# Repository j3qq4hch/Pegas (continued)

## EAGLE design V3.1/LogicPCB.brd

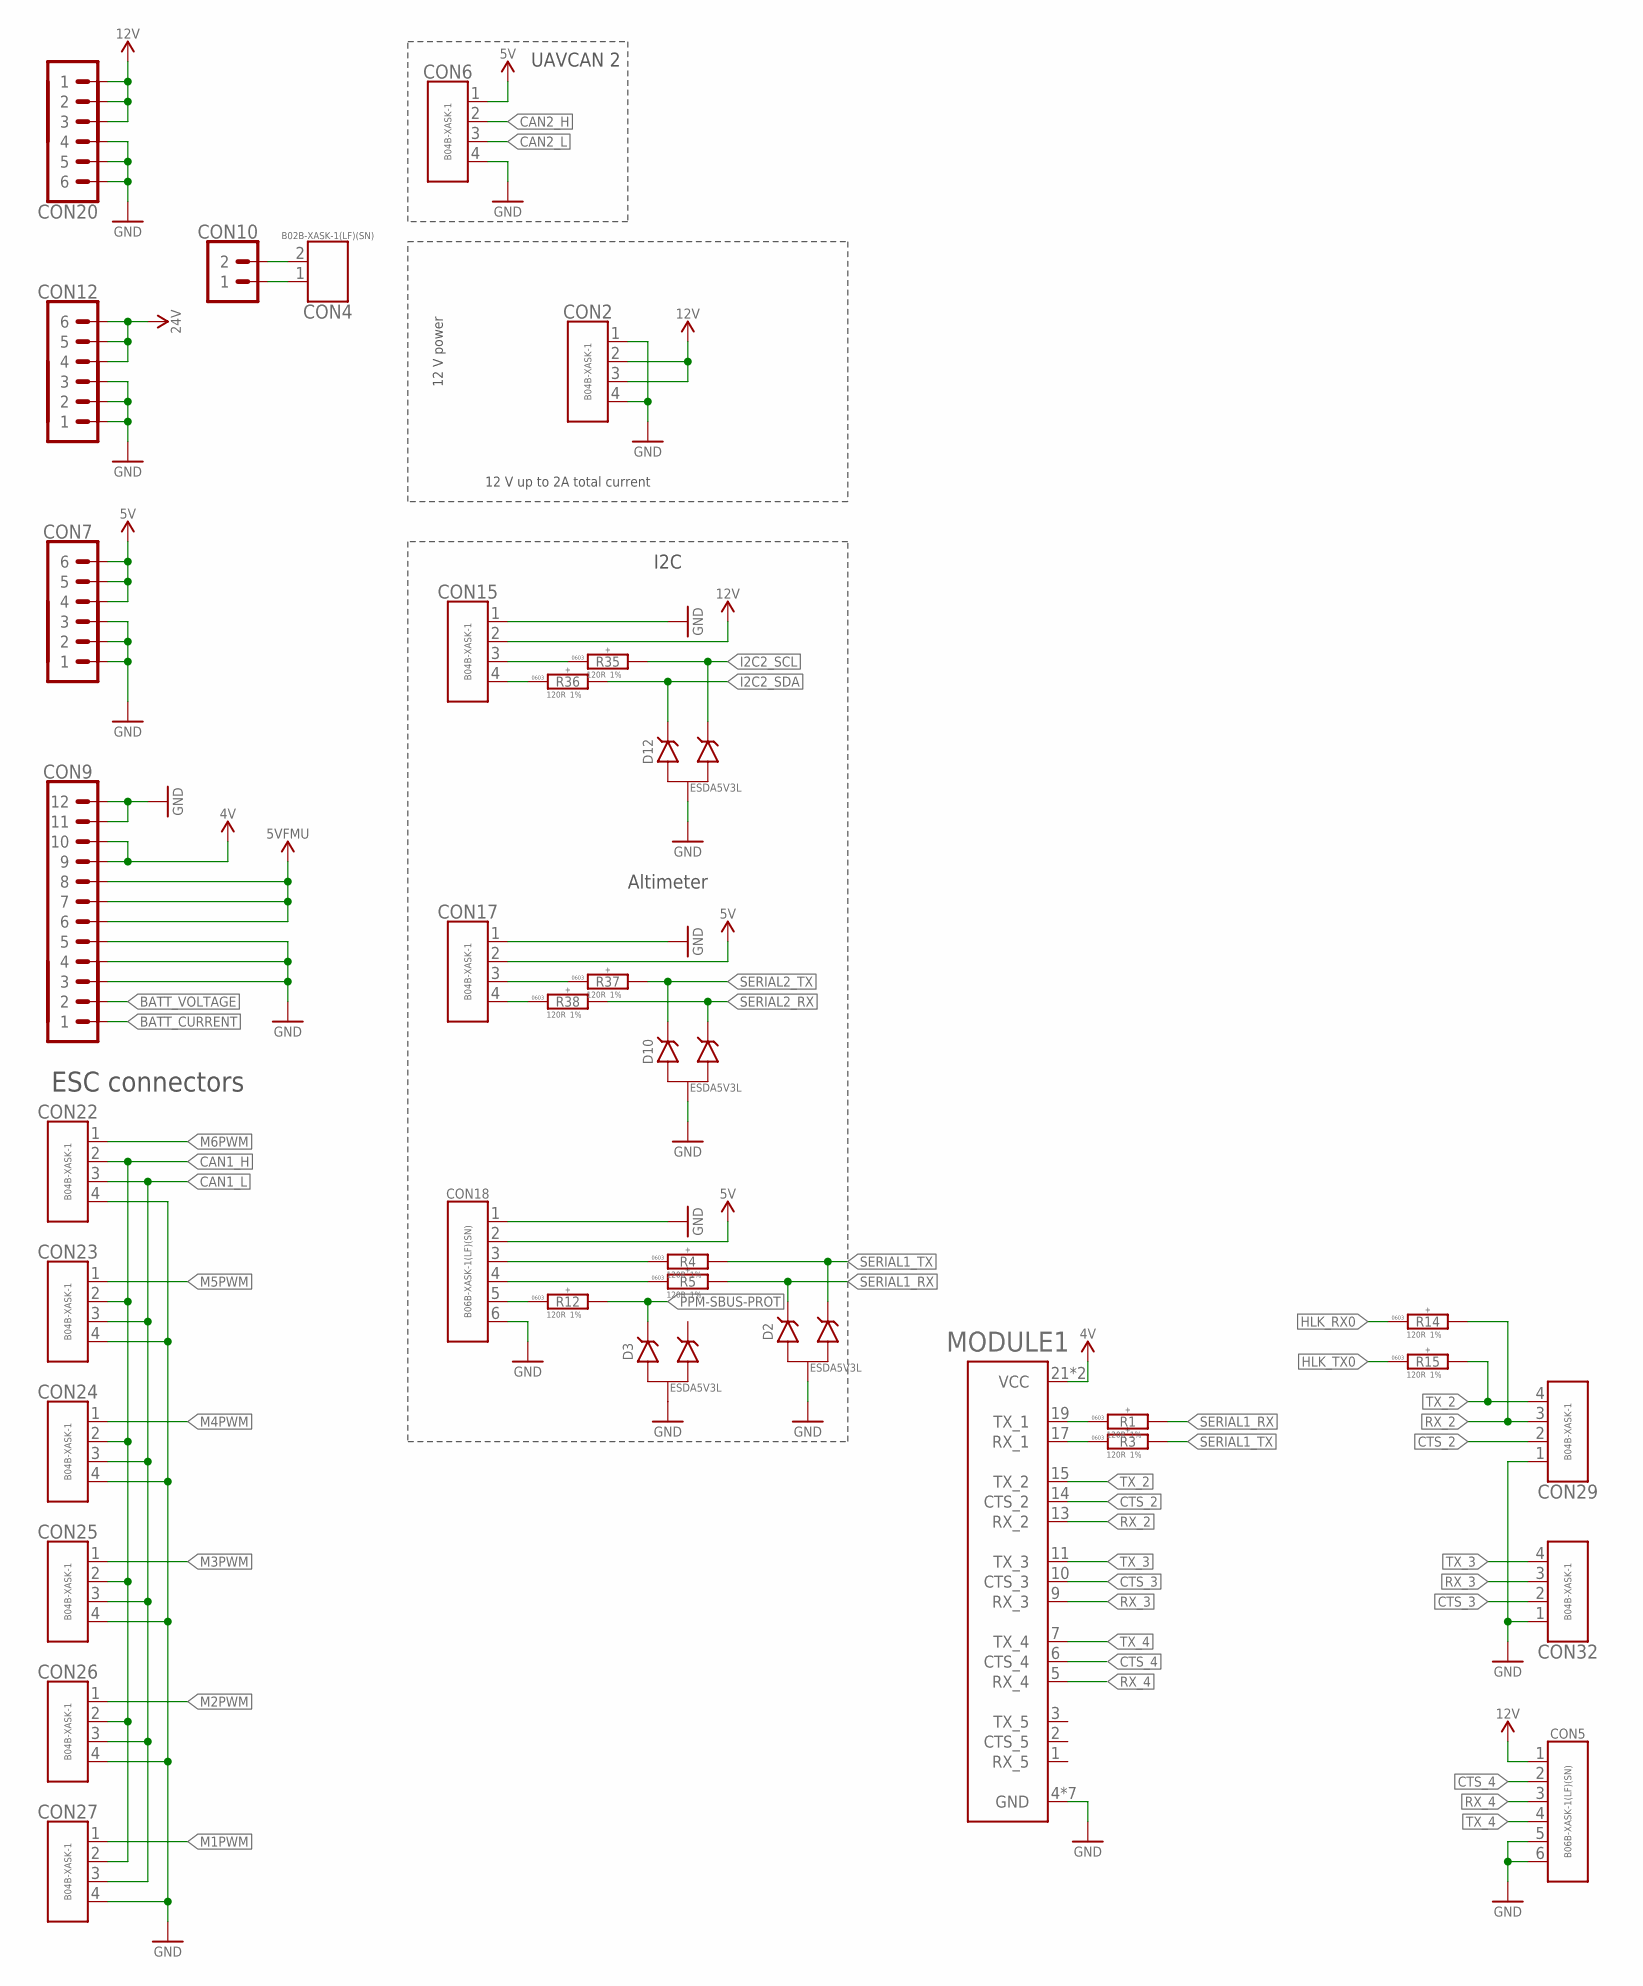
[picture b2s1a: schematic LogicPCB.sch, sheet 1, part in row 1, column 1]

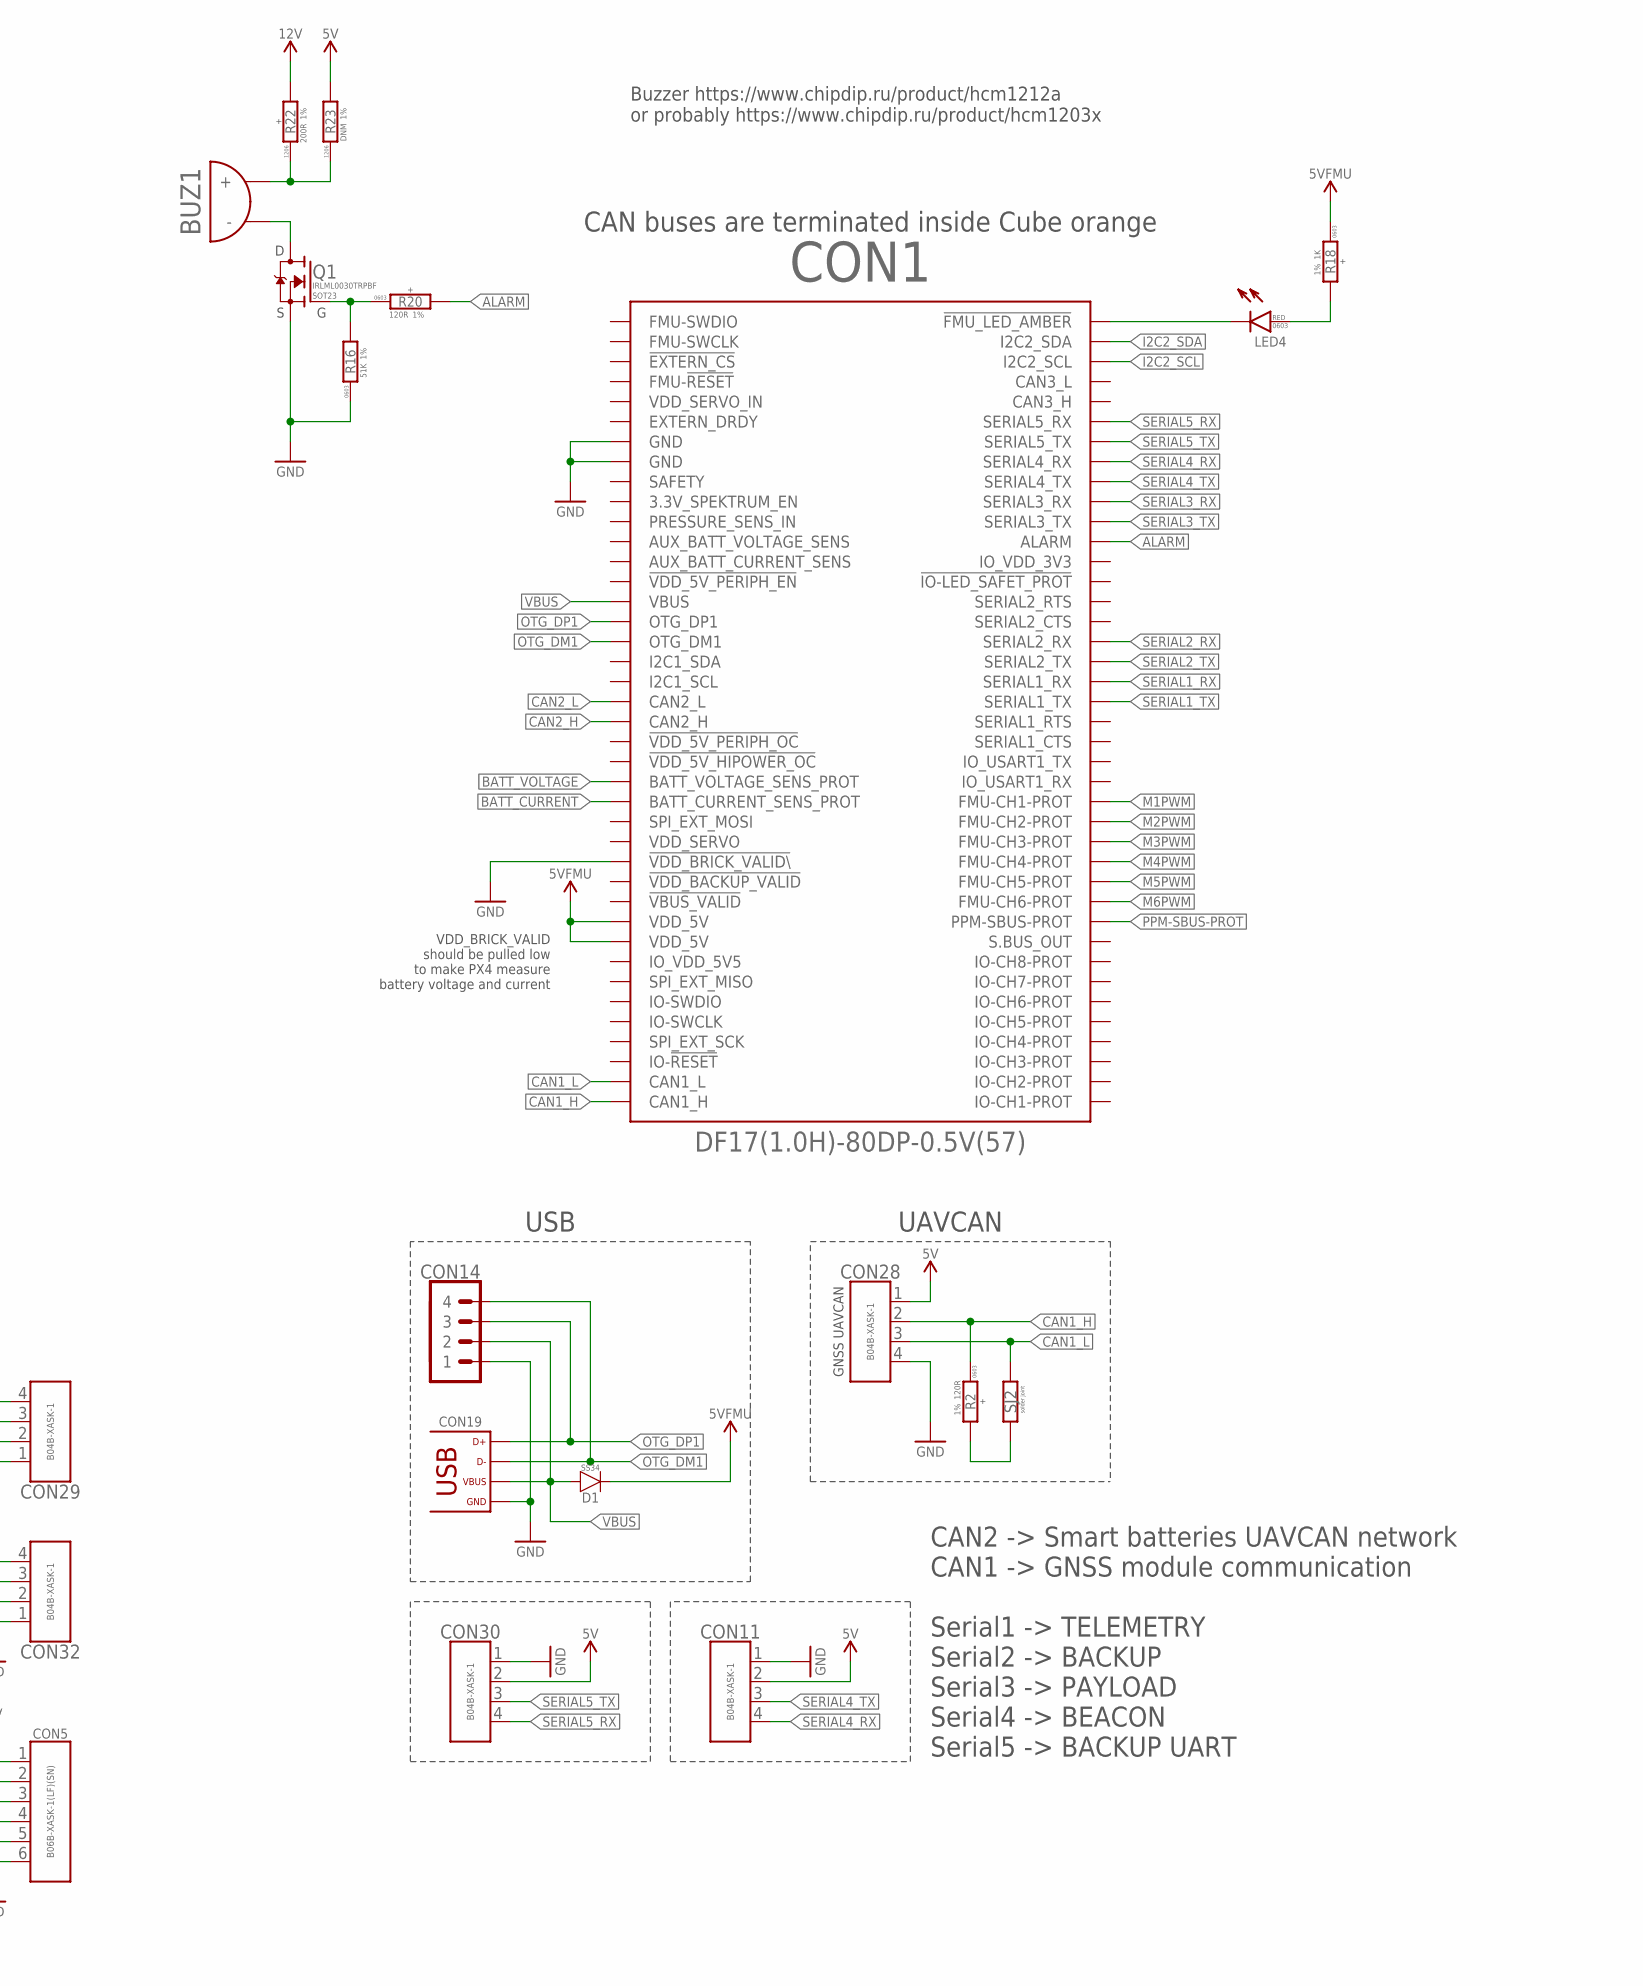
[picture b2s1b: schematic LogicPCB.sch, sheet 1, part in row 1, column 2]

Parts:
BUZ1: BUZZER-ЕР-12MM; BUZZER_12MM
CON1: CUBE_ORANGE_; CUBE_ORANGE
CON2, CON6, CON11, CON15, CON17, CON22, CON23, CON24, CON25, CON26, CON27, CON28, CON29, CON30, CON32: CON-4P-JST-XA; B04B-XASK-1
CON4: CON-2P-JST-XA; B02B-XASK-1
CON5, CON18: CON-6P-JST-XA; B06B-XASK-1
CON7, CON12, CON20: PINHEAD_1X06-2.54; 1X06-PTH-2.54
CON9: PINHEAD_1X12-2.54; 1X12-PTH-2.54
CON10: PINHEAD_1X02-2.54; 1X02-PTH-2.54
CON14: PINHEAD_1X04-2.54; 1X04-PTH-2.54
CON19: USB-TYPE-C-VERT-PROD; 2047110001-PROD; LCSC# C381139
D1: SS34; DO-214AC(SMA)
D2, D3, D10, D12: ESDA5V3L; SOT23B-3
LED4: LED-0603; LED0603; LCSC# C2286
MODULE1: MODEM_CARRIER
Q1: IRLML0030; SOT23
R1, R2, R3, R4, R5, R12, R14, R15, R20, R35, R36, R37, R38: 120R; R0603; LCSC# C22787
R16: 51K; R0603; LCSC# C23196
R18: 1K; R0603; LCSC# C21190
R22: 200R; R1206; LCSC# C25361
R23: DNM; R1206
SJ2: SOLDER_JOINT-SJ1; RES_0

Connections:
5VFMU: CON1.61 (VDD_5V), CON1.63 (VDD_5V), CON9.6, CON9.7, CON9.8, D1.C, R18.1
!FMU_LED_AMBER: CON1.2 (!FMU_LED_AMBER), LED4.C
ALARM: CON1.24 (ALARM), R20.2
BATT_CURRENT: CON1.49 (BATT_CURRENT_SENS_PROT), CON9.1
BATT_VOLTAGE: CON1.47 (BATT_VOLTAGE_SENS_PROT), CON9.2
CAN1_H: CON1.79 (CAN1_H), CON22.2, CON23.2, CON24.2, CON25.2, CON26.2, CON27.2, CON28.2, R2.1
CAN1_L: CON1.77 (CAN1_L), CON22.3, CON23.3, CON24.3, CON25.3, CON26.3, CON27.3, CON28.3, SJ2.2
CAN2_H: CON1.41 (CAN2_H), CON6.2
CAN2_L: CON1.39 (CAN2_L), CON6.3
CTS_2: CON29.2, MODULE1.14 (CTS_2)
CTS_3: CON32.2, MODULE1.10 (CTS_3)
CTS_4: CON5.2, MODULE1.6 (CTS_4)
GND: CON1.13 (GND), CON1.15 (GND), CON1.55 (!VDD_BRICK_VALID\), CON2.1, CON2.4, CON5.5, CON5.6, CON6.4, CON7.1, CON7.2, CON7.3, CON9.3, CON9.4, CON9.5, CON9.11, CON9.12, CON11.1, CON12.1, CON12.2, CON12.3, CON14.1, CON15.1, CON17.1, CON18.1, CON18.6, CON19.A1 (GND), CON19.A12 (GND), CON19.B1 (GND), CON19.B12 (GND), CON19.G1 (GND), CON19.G2 (GND), CON19.G4 (GND), CON19.G5 (GND), CON19.G7 (GND), CON19.G8 (GND), CON19.G9 (GND), CON19.G10 (GND), CON19.P$1 (GND), CON19.P$2 (GND), CON20.4, CON20.5, CON20.6, CON22.4, CON23.4, CON24.4, CON25.4, CON26.4, CON27.4, CON28.4, CON29.1, CON30.1, CON32.1, D2.3 (A), D3.3 (A), D10.3 (A), D12.3 (A), MODULE1.4 (GND), MODULE1.8 (GND), MODULE1.12 (GND), MODULE1.16 (GND), MODULE1.20 (GND), MODULE1.22 (GND), MODULE1.24 (GND), Q1.2 (S), R16.1; also elsewhere on the board
HLK_RX0: R14.1; also elsewhere on the board
HLK_TX0: R15.1; also elsewhere on the board
I2C2_SCL: CON1.6 (I2C2_SCL), D12.2 (C1), R35.2
I2C2_SDA: CON1.4 (I2C2_SDA), D12.1 (C), R36.2
M1PWM: CON1.50 (FMU-CH1-PROT), CON27.1
M2PWM: CON1.52 (FMU-CH2-PROT), CON26.1
M3PWM: CON1.54 (FMU-CH3-PROT), CON25.1
M4PWM: CON1.56 (FMU-CH4-PROT), CON24.1
M5PWM: CON1.58 (FMU-CH5-PROT), CON23.1
M6PWM: CON1.60 (FMU-CH6-PROT), CON22.1
unnamed: LED4.A, R18.2
unnamed: CON4.1, CON10.1
unnamed: BUZ1.2 (-), Q1.3 (D)
unnamed: MODULE1.19 (TX_1), R1.1
unnamed: Q1.1 (G), R16.2, R20.1
unnamed: MODULE1.17 (RX_1), R3.1
unnamed: CON4.2, CON10.2
unnamed: R2.2, SJ2.1
unnamed: CON18.3, R4.1
unnamed: CON18.4, R5.1
unnamed: BUZ1.1 (+), R22.P$1 (1), R23.P$1 (1)
unnamed: CON18.5, R12.1
unnamed: CON15.3, R35.1
unnamed: CON15.4, R36.1
unnamed: CON17.3, R37.1
unnamed: CON17.4, R38.1
OTG_DM1: CON1.33 (OTG_DM1), CON14.4, CON19.A7 (D-), CON19.B7 (D-)
OTG_DP1: CON1.31 (OTG_DP1), CON14.3, CON19.A6 (D+), CON19.B6 (D+)
PPM-SBUS-PROT: CON1.62 (PPM-SBUS-PROT), D3.1 (C), R12.2
RX_2: CON29.3, MODULE1.13 (RX_2), R14.2
RX_3: CON32.3, MODULE1.9 (RX_3)
RX_4: CON5.3, MODULE1.5 (RX_4)
SERIAL1_RX: CON1.38 (SERIAL1_RX), D2.1 (C), R1.2, R5.2; also elsewhere on the board
SERIAL1_TX: CON1.40 (SERIAL1_TX), D2.2 (C1), R3.2, R4.2; also elsewhere on the board
SERIAL2_RX: CON1.34 (SERIAL2_RX), D10.2 (C1), R38.2
SERIAL2_TX: CON1.36 (SERIAL2_TX), D10.1 (C), R37.2
SERIAL3_RX: CON1.20 (SERIAL3_RX); also elsewhere on the board
SERIAL3_TX: CON1.22 (SERIAL3_TX); also elsewhere on the board
SERIAL4_RX: CON1.16 (SERIAL4_RX), CON11.4
SERIAL4_TX: CON1.18 (SERIAL4_TX), CON11.3
SERIAL5_RX: CON1.12 (SERIAL5_RX), CON30.4
SERIAL5_TX: CON1.14 (SERIAL5_TX), CON30.3
TX_2: CON29.4, MODULE1.15 (TX_2), R15.2
TX_3: CON32.4, MODULE1.11 (TX_3)
TX_4: CON5.4, MODULE1.7 (TX_4)
VBUS: CON1.29 (VBUS), CON14.2, CON19.A4 (VBUS), CON19.B4 (VBUS), D1.A
VDD_4V: CON9.9, CON9.10, MODULE1.21 (VCC), MODULE1.23 (VCC)
VDD_5V: CON6.1, CON7.4, CON7.5, CON7.6, CON11.2, CON17.2, CON18.2, CON28.1, CON30.2, R23.P$2 (2)
VDD_12V: CON2.2, CON2.3, CON5.1, CON15.2, CON20.1, CON20.2, CON20.3, R22.P$2 (2); also elsewhere on the board
VDD_24V: CON12.4, CON12.5, CON12.6; also elsewhere on the board

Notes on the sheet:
12 V up to 2A total current
12 V power
GNSS UAVCAN
UAVCAN
UAVCAN 2
CAN buses are terminated inside Cube orange
CAN2 -> Smart batteries UAVCAN network CAN1 -> GNSS module communication Serial1 -> TELEMETRY Serial2 -> BACKUP Serial3 -> PAYLOAD Serial4 -> BEACON Serial5 -> BACKUP UART
USB
VDD_BRICK_VALID should be pulled low to make PX4 measure battery voltage and current
Buzzer https://www.chipdip.ru/product/hcm1212a or probably https://www.chipdip.ru/product/hcm1203x
ESC connectors
Altimeter
I2C

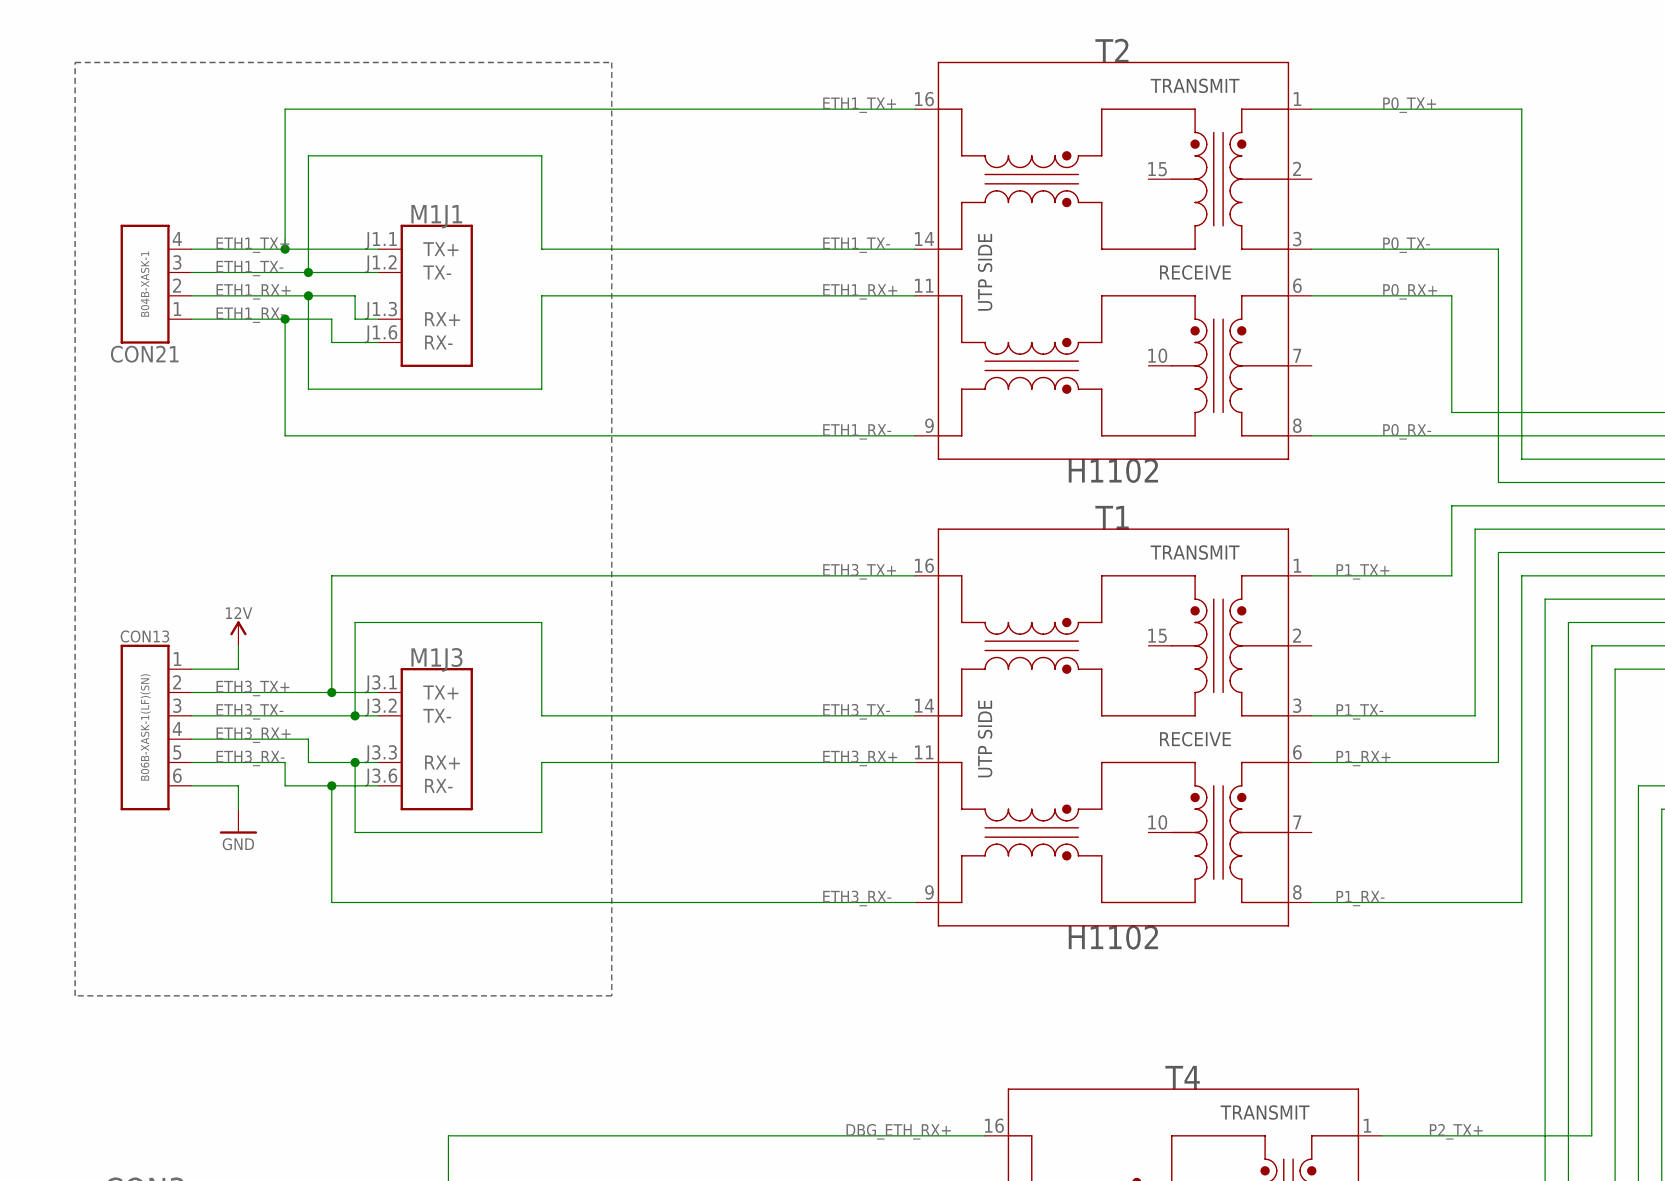
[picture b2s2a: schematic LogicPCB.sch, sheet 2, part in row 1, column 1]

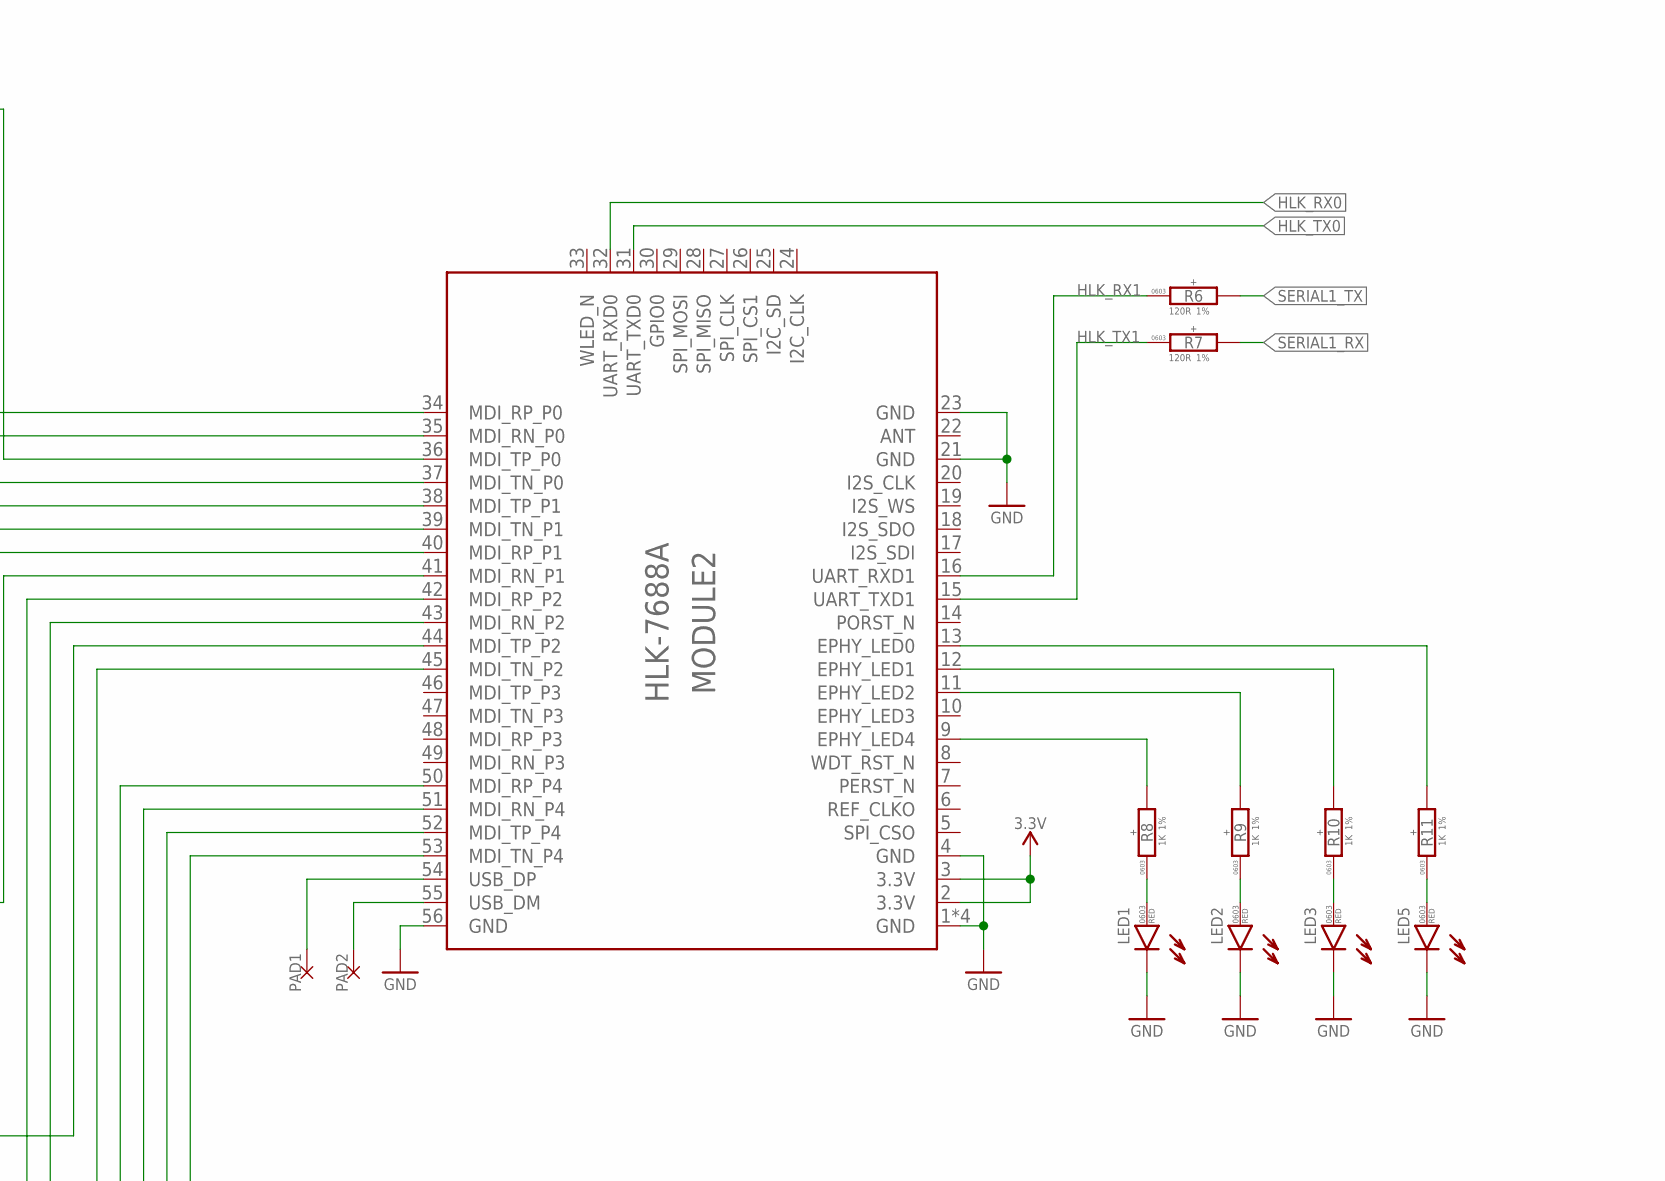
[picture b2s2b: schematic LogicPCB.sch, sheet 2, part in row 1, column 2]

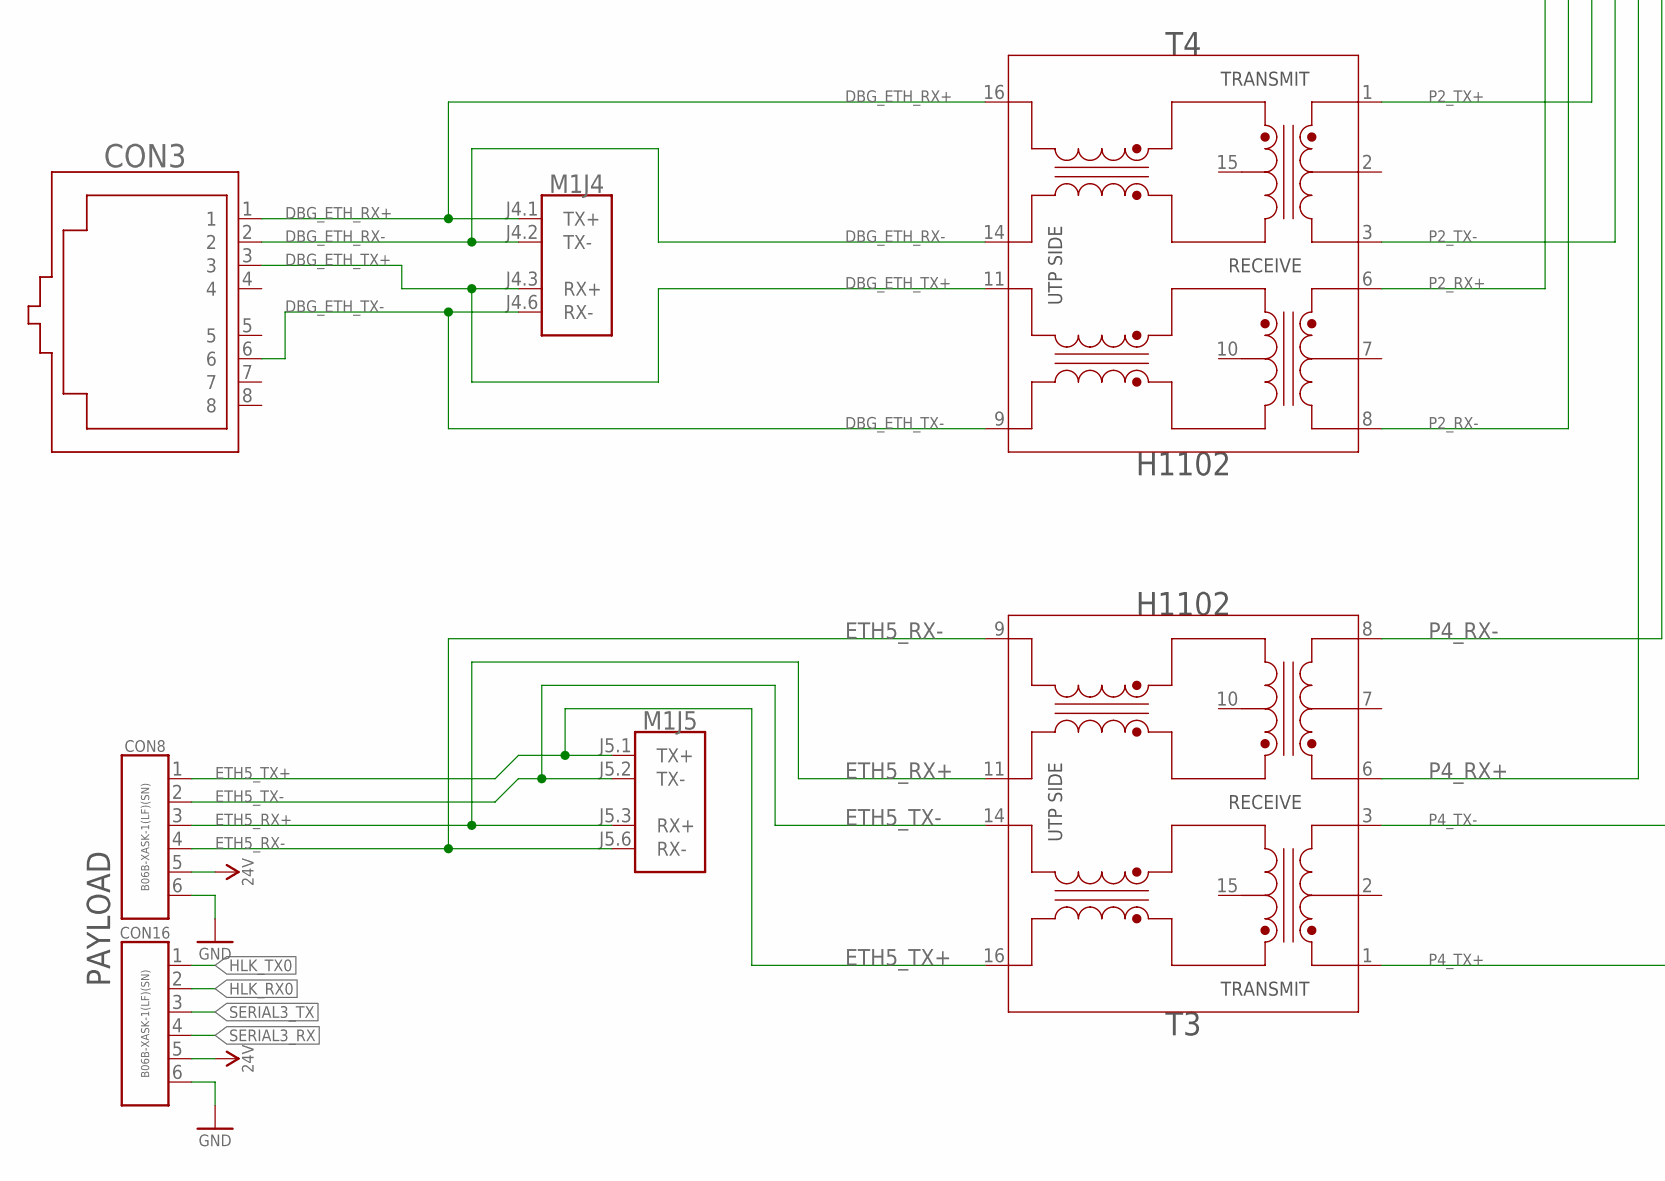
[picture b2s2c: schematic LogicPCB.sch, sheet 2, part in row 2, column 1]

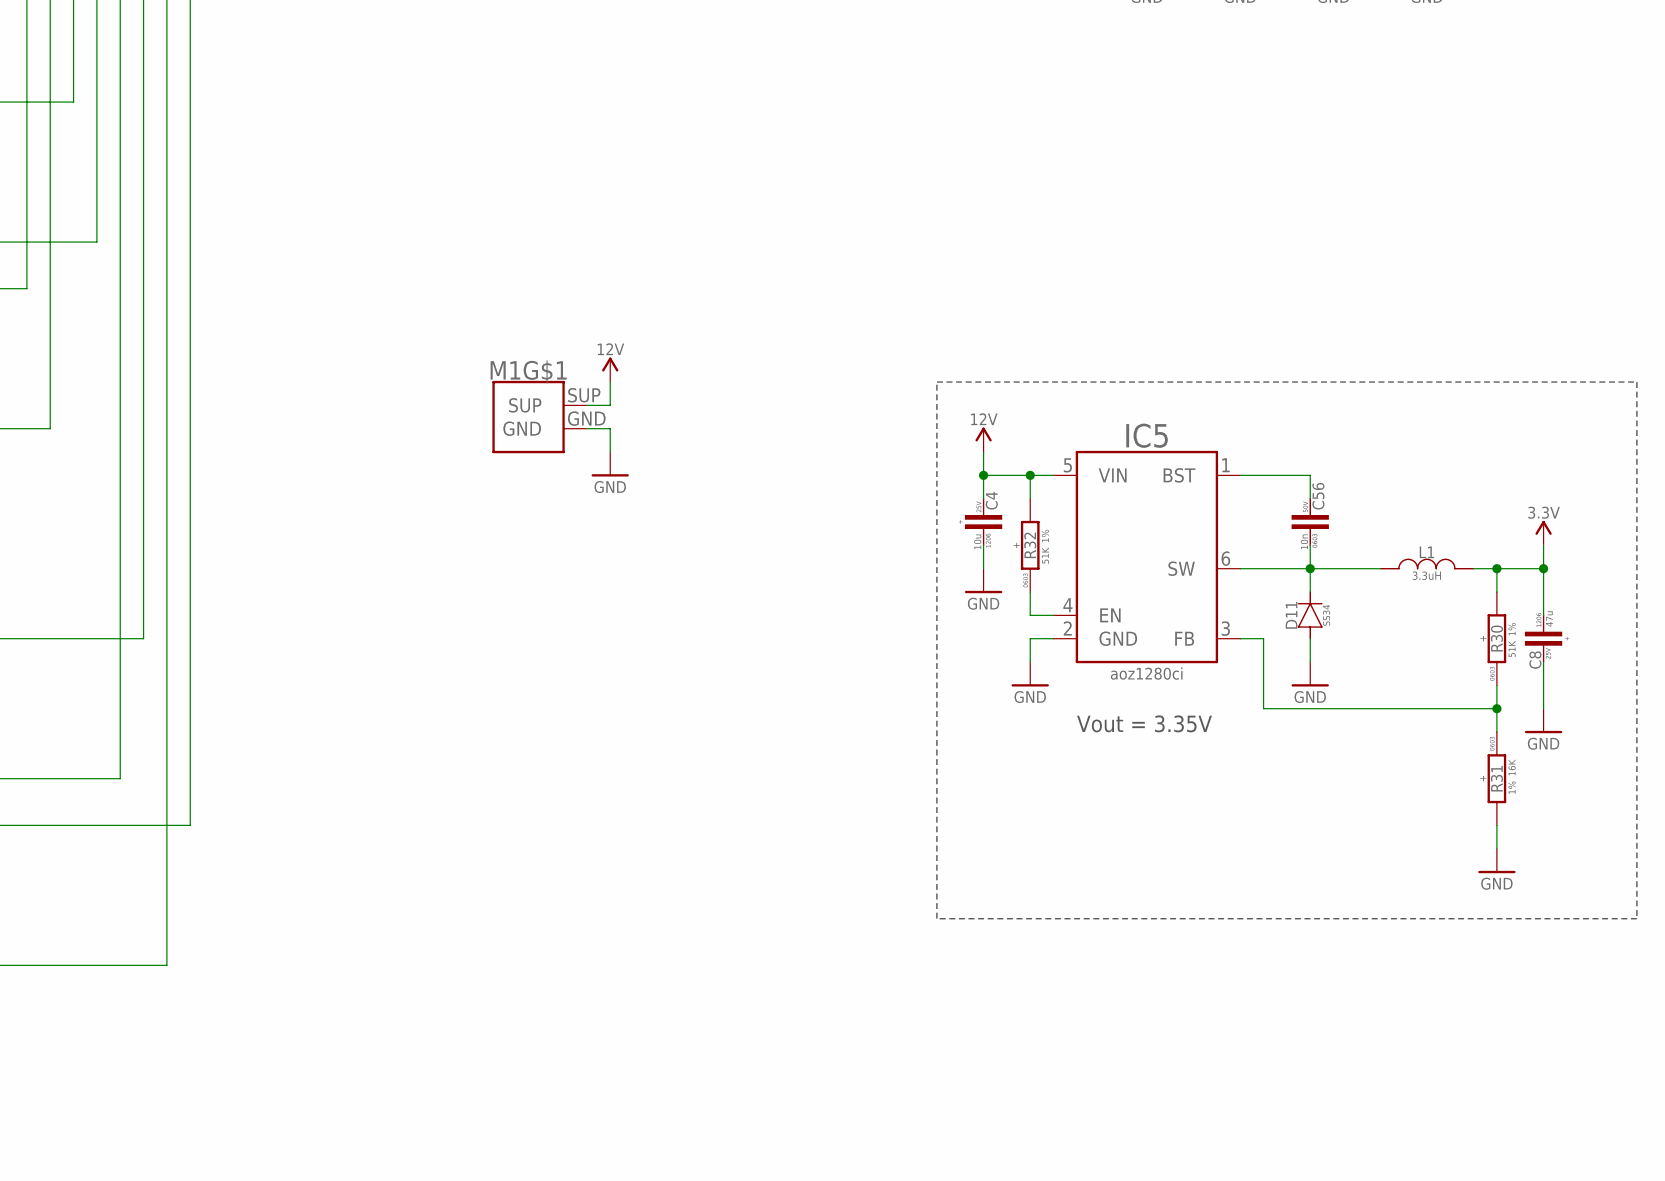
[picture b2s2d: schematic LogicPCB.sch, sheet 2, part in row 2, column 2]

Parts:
C4: 10u; C1206; VOLTAGE 25V; LCSC# C77090
C8: 47u; C1206; VOLTAGE 25V; LCSC# C403725
C56: 10n; C0603; VOLTAGE 50V
CON3: RJ45-NO_SHIELD-5556416-1; 5556416-1
CON8, CON13, CON16: CON-6P-JST-XA; B06B-XASK-1
CON21: CON-4P-JST-XA; B04B-XASK-1
D11: SS34; DO-214AC(SMA)
IC5: AOZ1280; SOT23-6
L1: 3.3uH; IHLP-2020BZ-01
LED1, LED2, LED3, LED5: LED-0603; LED0603; LCSC# C2286
M1: 05G_ETHERNET_SWITCH; 05G_ETH_SWITCH
MODULE2: HLK-7688A
PAD1, PAD2: PAD-HEX-2MM; HEX-2MM
R6, R7: 120R; R0603; LCSC# C22787
R8, R9, R10, R11: 1K; R0603; LCSC# C21190
R30, R32: 51K; R0603; LCSC# C23196
R31: 16K; R0603; LCSC# C25804
T1, T2, T3, T4: H1102NL; H1102

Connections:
DBG_ETH_RX+: CON3.1, M1.J4.1 (TX+), T4.16
DBG_ETH_RX-: CON3.2, M1.J4.2 (TX-), T4.14
DBG_ETH_TX+: CON3.3, M1.J4.3 (RX+), T4.11
DBG_ETH_TX-: CON3.6, M1.J4.6 (RX-), T4.9
ETH1_RX+: CON21.2, M1.J1.3 (RX+), T2.11
ETH1_RX-: CON21.1, M1.J1.6 (RX-), T2.9
ETH1_TX+: CON21.4, M1.J1.1 (TX+), T2.16
ETH1_TX-: CON21.3, M1.J1.2 (TX-), T2.14
ETH3_RX+: CON13.4, M1.J3.3 (RX+), T1.11
ETH3_RX-: CON13.5, M1.J3.6 (RX-), T1.9
ETH3_TX+: CON13.2, M1.J3.1 (TX+), T1.16
ETH3_TX-: CON13.3, M1.J3.2 (TX-), T1.14
ETH5_RX+: CON8.3, M1.J5.3 (RX+), T3.11
ETH5_RX-: CON8.4, M1.J5.6 (RX-), T3.9
ETH5_TX+: CON8.1, M1.J5.1 (TX+), T3.16
ETH5_TX-: CON8.2, M1.J5.2 (TX-), T3.14
GND: C4.P$1 (1), C8.P$2 (2), CON8.6, CON13.6, CON16.6, D11.A, IC5.2 (GND), LED1.C, LED2.C, LED3.C, LED5.C, M1.GND, MODULE2.1 (GND), MODULE2.4 (GND), MODULE2.21 (GND), MODULE2.23 (GND), MODULE2.56 (GND), MODULE2.P$1 (GND), MODULE2.P$2 (GND), MODULE2.P$3 (GND), R31.2; also elsewhere on the board
HLK_RX0: CON16.2, MODULE2.32 (UART_RXD0); also elsewhere on the board
HLK_RX1: MODULE2.16 (UART_RXD1), R6.1
HLK_TX0: CON16.1, MODULE2.31 (UART_TXD0); also elsewhere on the board
HLK_TX1: MODULE2.15 (UART_TXD1), R7.1
LINK2: MODULE2.11 (EPHY_LED2), R9.2
LINK4: MODULE2.9 (EPHY_LED4), R8.2
unnamed: LED1.A, R8.1
unnamed: LED2.A, R9.1
unnamed: LED3.A, R10.1
unnamed: LED5.A, R11.1
unnamed: MODULE2.12 (EPHY_LED1), R10.2
unnamed: MODULE2.13 (EPHY_LED0), R11.2
unnamed: C56.2, IC5.1 (BST)
unnamed: IC5.3 (FB), R30.1, R31.1
unnamed: IC5.4 (EN), R32.1
P0_RX+: MODULE2.34 (MDI_RP_P0), T2.6
P0_RX-: MODULE2.35 (MDI_RN_P0), T2.8
P0_TX+: MODULE2.36 (MDI_TP_P0), T2.1
P0_TX-: MODULE2.37 (MDI_TN_P0), T2.3
P1_RX+: MODULE2.40 (MDI_RP_P1), T1.6
P1_RX-: MODULE2.41 (MDI_RN_P1), T1.8
P1_TX+: MODULE2.38 (MDI_TP_P1), T1.1
P1_TX-: MODULE2.39 (MDI_TN_P1), T1.3
P2_RX+: MODULE2.42 (MDI_RP_P2), T4.6
P2_RX-: MODULE2.43 (MDI_RN_P2), T4.8
P2_TX+: MODULE2.44 (MDI_TP_P2), T4.1
P2_TX-: MODULE2.45 (MDI_TN_P2), T4.3
P4_RX+: MODULE2.50 (MDI_RP_P4), T3.6
P4_RX-: MODULE2.51 (MDI_RN_P4), T3.8
P4_TX+: MODULE2.52 (MDI_TP_P4), T3.1
P4_TX-: MODULE2.53 (MDI_TN_P4), T3.3
SERIAL1_RX: R7.2; also elsewhere on the board
SERIAL1_TX: R6.2; also elsewhere on the board
SERIAL3_RX: CON16.4; also elsewhere on the board
SERIAL3_TX: CON16.3; also elsewhere on the board
SW: C56.1, D11.C, IC5.6 (SW), L1.P$1 (1)
USB_DM: MODULE2.55 (USB_DM), PAD2.1
USB_DP: MODULE2.54 (USB_DP), PAD1.1
VDD_3V3: C8.P$1 (1), L1.P$2 (2), MODULE2.2 (3.3V), MODULE2.3 (3.3V), R30.2
VDD_12V: C4.P$2 (2), CON13.1, IC5.5 (VIN), M1.SUP, R32.2; also elsewhere on the board
VDD_24V: CON8.5, CON16.5; also elsewhere on the board

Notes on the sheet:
Vout = 3.35V
PAYLOAD

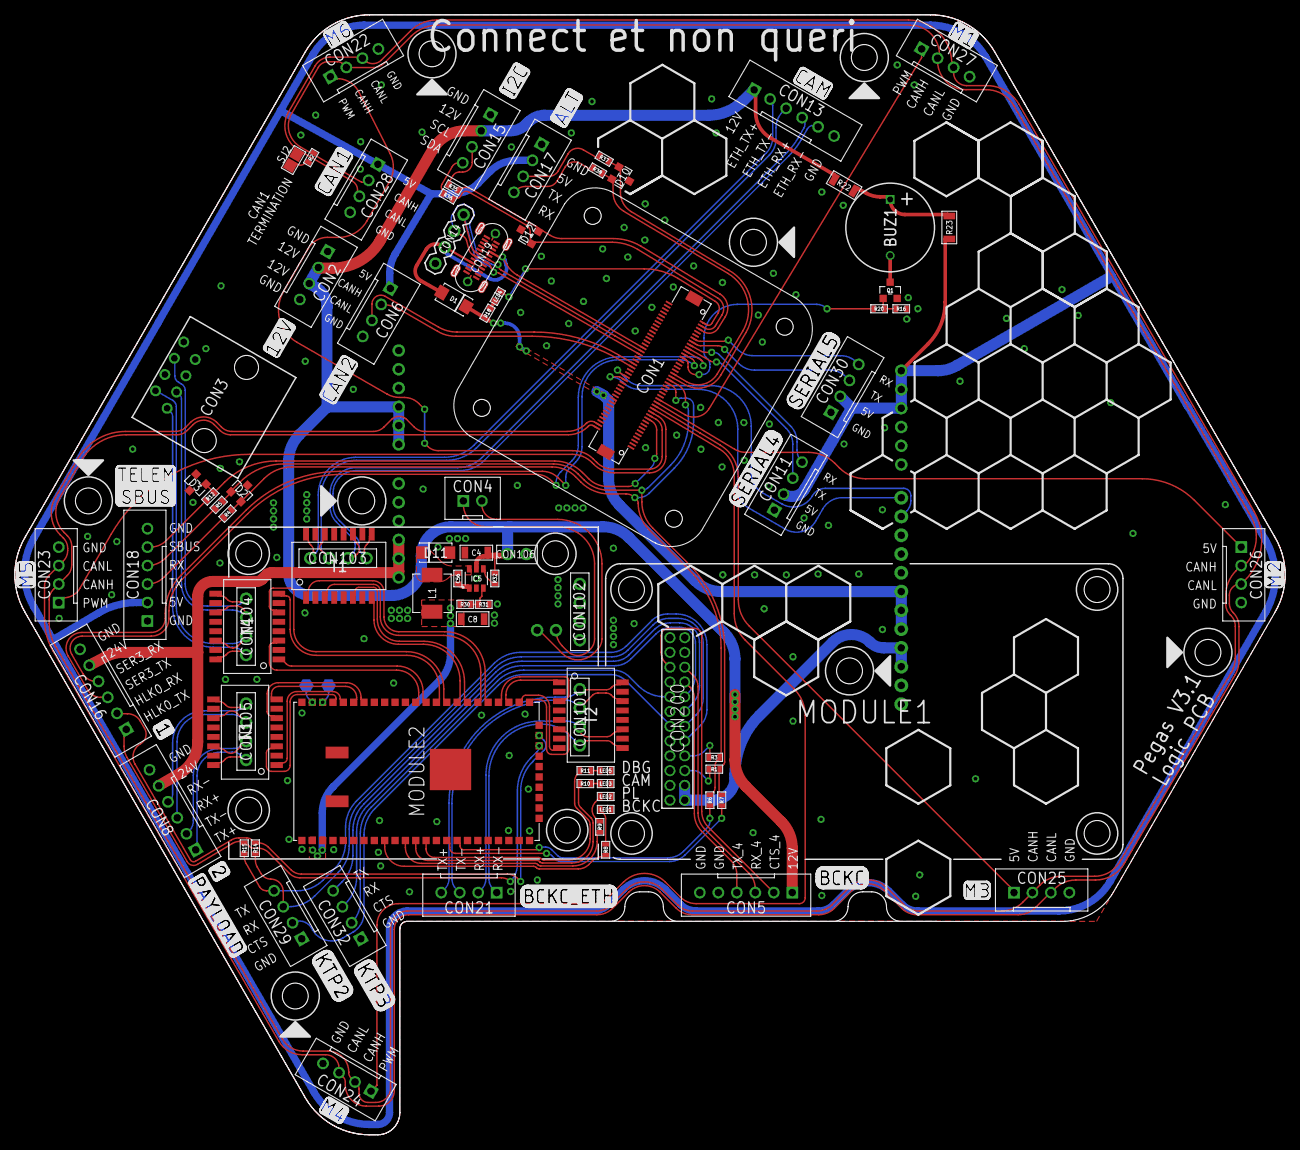
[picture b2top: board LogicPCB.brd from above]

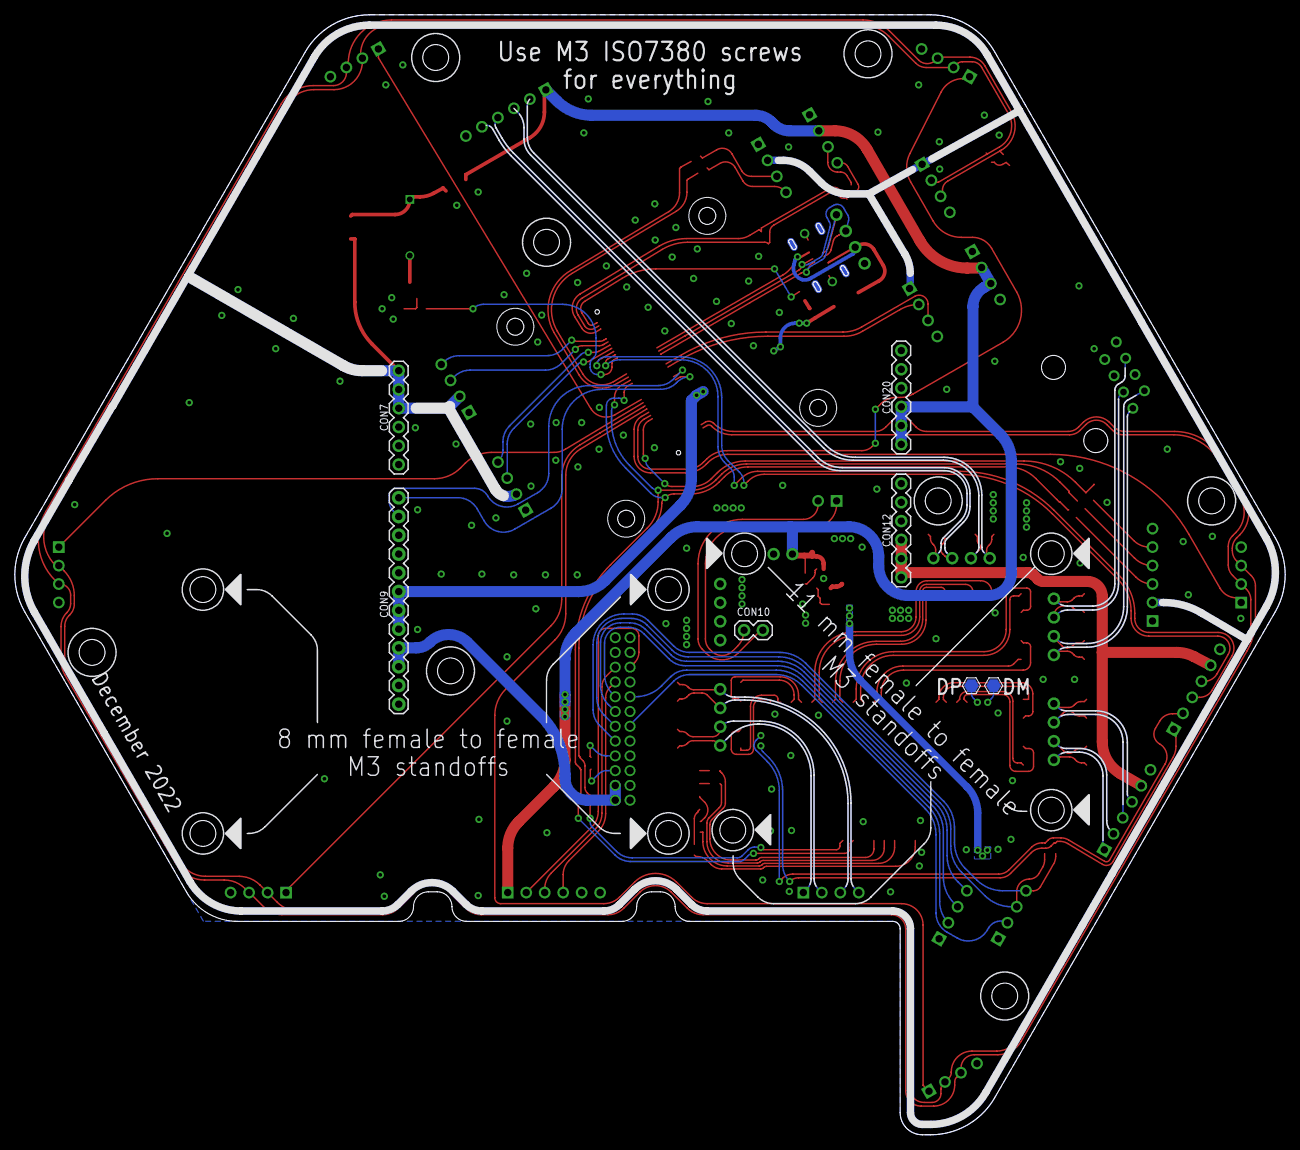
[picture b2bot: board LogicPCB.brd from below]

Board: 2 copper layers, 171.9 x 151.6 mm, 85 parts (7 on the bottom side), 112 nets.
